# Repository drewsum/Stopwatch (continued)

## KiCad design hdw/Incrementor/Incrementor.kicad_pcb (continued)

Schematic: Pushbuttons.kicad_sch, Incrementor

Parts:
C701, C705, C706: 10nF; C_0603; Voltage 50V; Digi-Key PN 1276-1921-1-ND
C702, C703, C704, C707, C708, C709, C712, C713, C715, C717: 0.1uF; C_0603; Voltage 50V; Digi-Key PN 311-1344-1-ND
C710, C711, C714: 10uF; C_0603; Voltage 10V; Digi-Key PN 490-14372-1-ND
R701, R702, R703: 499; R_0603; Tolerance 1%; Digi-Key PN P499HCT-ND
R704, R705, R706, R707, R708, R709, R710, R711, R712: 10k; R_0603; Tolerance 1%; Digi-Key PN RMCF0603FT10K0CT-ND
SW701, SW702, SW703: Cap_Touch; Capacitive_Touch_Pad
U701, U707, U708: AT42QT1010-TSHR; SOT-23-6; Digi-Key PN AT42QT1010-TSHRCT-ND
U702, U703, U706: TLV71330PDBV; SOT-23-5; Digi-Key PN 296-40658-1-ND
U704: 74LVC1G80; SOT-353_SC-70-5; Digi-Key PN 296-9852-1-ND
U705, U709, U710: 74LVC1G17; SOT-353_SC-70-5; Digi-Key PN 296-11934-1-ND

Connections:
+3V3: C702.1, C703.1, C704.1, C712.1, C713.1, C715.1, C717.1, U702.1 (IN), U702.3 (EN), U703.1 (IN), U703.3 (EN), U704.5 (VCC), U705.5 (VCC), U706.1 (IN), U706.3 (EN), U709.5 (VCC), U710.5 (VCC); also elsewhere on the board
Count_Reset: R712.1, U709.4; also elsewhere on the board
Display_Enable: R705.1, U704.1 (D), U704.4 (~Q); also elsewhere on the board
GND: C702.2, C703.2, C704.2, C707.2, C708.2, C709.2, C710.2, C711.2, C712.2, C713.2, C714.2, C715.2, C717.2, R704.2, R705.2, R706.2, R707.2, R711.2, R712.2, U701.2 (VSS), U702.2 (GND), U703.2 (GND), U704.3 (GND), U705.3 (GND), U706.2 (GND), U707.2 (VSS), U708.2 (VSS), U709.3 (GND), U710.3 (GND); also elsewhere on the board
unnamed: C701.1, U701.4 (SNS)
unnamed: C701.2, R701.2, U701.3 (SNSK)
unnamed: C705.1, U707.4 (SNS)
unnamed: C705.2, R702.2, U707.3 (SNSK)
unnamed: C706.1, U708.4 (SNS)
unnamed: C706.2, R703.2, U708.3 (SNSK)
unnamed: C707.1, U701.5 (VDD), U701.6 (SYNC), U702.5 (OUT)
unnamed: C708.1, U703.5 (OUT), U707.5 (VDD), U707.6 (SYNC)
unnamed: C709.1, U706.5 (OUT), U708.5 (VDD), U708.6 (SYNC)
unnamed: C710.1, R709.1, U709.2
unnamed: C711.1, R710.1, U710.2
unnamed: C714.1, R708.1, U705.2
unnamed: R701.1, SW701.1
unnamed: R702.1, SW702.1
unnamed: R703.1, SW703.1
unnamed: R704.1, R708.2, U701.1 (OUT)
unnamed: R706.1, R709.2, U707.1 (OUT)
unnamed: R707.1, R710.2, U708.1 (OUT)
unnamed: R711.1, U704.2 (C), U705.4
Source_Select: U710.4; also elsewhere on the board

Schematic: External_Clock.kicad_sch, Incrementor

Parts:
C801: 0.1uF; C_0603; Voltage 50V; Digi-Key PN 311-1344-1-ND
D801: 3.3V; D_SOD-323; Digi-Key PN CDSOD323-T03SCT-ND
J801: CLK_IN; Socket_Strip_Angled_1x02_Pitch2.54mm; Digi-Key PN SAM1225-02-ND
R801, R803: 100; R_0603; Tolerance 1%; Digi-Key PN RMCF0603FT100RCT-ND
R802: 10k; R_0603; Tolerance 1%; Digi-Key PN RMCF0603FT10K0CT-ND
U801: 74LVC1G17; SOT-353_SC-70-5; Digi-Key PN 296-11934-1-ND

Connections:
+3V3: C801.1, R802.1, U801.5 (VCC); also elsewhere on the board
External_Clock: U801.4; also elsewhere on the board
GND: C801.2, D801.2 (A2), J801.2, U801.3 (GND); also elsewhere on the board
unnamed: D801.1 (A1), R801.2, R802.2, R803.1
unnamed: J801.1, R801.1
unnamed: R803.2, U801.2

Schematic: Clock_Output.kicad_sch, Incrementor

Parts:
C1901: 0.1uF; C_0603; Voltage 50V; Digi-Key PN 311-1344-1-ND
D1901: 3.3V; D_SOD-323; Digi-Key PN CDSOD323-T03SCT-ND
J1901: CLK_OUT; Socket_Strip_Angled_1x02_Pitch2.54mm; Digi-Key PN SAM1225-02-ND
R1901, R1903: 100; R_0603; Tolerance 1%; Digi-Key PN RMCF0603FT100RCT-ND
R1902: 10k; R_0603; Tolerance 1%; Digi-Key PN RMCF0603FT10K0CT-ND
U1901: 74LVC1G17; SOT-353_SC-70-5; Digi-Key PN 296-11934-1-ND

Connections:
+3V3: C1901.1, R1902.1, U1901.5 (VCC); also elsewhere on the board
GND: C1901.2, D1901.2 (A2), J1901.2, U1901.3 (GND); also elsewhere on the board
unnamed: D1901.1 (A1), R1901.2, R1902.2, R1903.1
unnamed: J1901.1, R1903.2
unnamed: R1901.1, U1901.4
Stage10_Clock_Out: U1901.2; also elsewhere on the board

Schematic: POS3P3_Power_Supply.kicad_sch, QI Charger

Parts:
C301: 10uF; C_1206; Voltage 25V; Digi-Key PN 1276-7031-1-ND
C302: 10nF; C_0603; Voltage 50V; Digi-Key PN 1276-1921-1-ND
C303: 0.1uF; C_0603; Voltage 50V; Digi-Key PN 490-8020-1-ND
C307, C308: 22uF; C_1206; Voltage 10V; Digi-Key PN 1276-3148-1-ND
L301: 2.2u; L_Vishay_IHLP-2020; Tolerance 20%; Digi-Key PN 541-1236-1-ND
R301: 10k; R_0603; Tolerance 1%; Digi-Key PN RHM10KADCT-ND
R302: 100k; R_0603; Tolerance 1%; Digi-Key PN A106046CT-ND
R303: 10.5k; R_0603; Tolerance 1%; Digi-Key PN 311-10.5KHRCT-ND
R304: 562k; R_0603; Tolerance 1%; Digi-Key PN 311-562KHRCT-ND
R305: 180k; R_0603; Tolerance 1%; Digi-Key PN 749-1763-1-ND
TP301: TP; Test_Point
U301: TPS62130; QFN-16-1EP_3x3mm_Pitch0.5mm; Digi-Key PN 296-37878-1-ND

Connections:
+3V3: L301.2, R301.1, R304.1, TP301.1, U301.14 (VOS); also elsewhere on the board
+12V: C301.1, C303.1, R302.1, U301.10 (AVIN), U301.11 (PVIN), U301.12 (PVIN); also elsewhere on the board
GND: C301.2, C302.2, C303.2, R303.2, R305.2, U301.6 (AGND), U301.7 (FSW), U301.8 (DEF), U301.15 (PGND), U301.16 (PGND), U301.17 (EP); also elsewhere on the board
unnamed: C302.1, U301.9 (SS/TR)
unnamed: L301.1, U301.1 (SW), U301.2 (SW), U301.3 (SW)
unnamed: R302.2, R303.1, U301.13 (EN)
unnamed: R304.2, R305.1, U301.5 (FB)
POS3P3_PGOOD: R301.2, U301.4 (PG); also elsewhere on the board

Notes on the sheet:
03. +5V Power Supply

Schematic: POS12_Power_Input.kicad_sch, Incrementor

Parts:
C201: 0.1uF; C_0603; Voltage 50V; Digi-Key PN 311-1344-1-ND
C202, C204: 10nF; C_0603; Voltage 50V; Digi-Key PN 1276-1921-1-ND
C203: 1nF; C_0603; Voltage 50V; Digi-Key PN 1276-1018-1-ND
C205: 100uF; CP_Tantalum_Case-X_EIA-7343-43_Reflow; Voltage 16V; Tolerance 10%; Digi-Key PN 718-1102-1-ND
D201: 24V; D_SMA; Digi-Key PN SMAJ24CALFCT-ND
J201: +12V IN; BARREL_JACK; Digi-Key PN CP-202BH-ND
N201: +12V 1A Power Supply; Digi-Key PN 993-1335-ND
R201: 51.1k; R_0603; Tolerance 1%; Digi-Key PN RMCF0603FT10K0CT-ND
R202: 1.15k; R_0603; Tolerance 1%; Digi-Key PN RMCF0603FT10K0CT-ND
R203: 5.11k; R_0603; Tolerance 1%; Digi-Key PN RMCF0603FT10K0CT-ND
R204, R206: 10k; R_0603; Tolerance 1%; Digi-Key PN RMCF0603FT10K0CT-ND
R205: 6.04k; R_0603; Tolerance 1%; Digi-Key PN RMCF0603FT10K0CT-ND
R207: 16.5k; R_0603; Tolerance 1%; Digi-Key PN RMCF0603FT10K0CT-ND
TP201: TP; Pin_Header_Angled_1x01_Pitch2.54mm; Digi-Key PN 36-5005-ND
TP202, TP203: TP_Pad; Test_Point
U201: TPS26600RHFT; QFN-24-1EP_4x5mm_Pitch0.5mm; Digi-Key PN 296-45478-1-ND

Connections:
+3V3: R206.1; also elsewhere on the board
+12V: C205.1, TP203.1, U201.23 (OUT), U201.24 (OUT); also elsewhere on the board
+12Vin: C201.1, C202.1, C203.1, D201.1 (A1), J201.1, R201.1, R204.1, TP202.1, U201.8 (IN), U201.9 (IN)
GND: C201.2, C202.2, C203.2, C205.2, D201.2 (A2), J201.2, J201.3, TP201.1, U201.17 (GND); also elsewhere on the board
unnamed: C204.1, U201.20 (dVdT)
unnamed: C204.2, R203.2, R205.2, R207.2, U201.15 (RTN), U201.25 (RTN_PAD)
unnamed: R201.2, R202.1, U201.10 (UVLO)
unnamed: R202.2, R203.1, U201.12 (NC)
unnamed: R204.2, U201.14 (~SHDN)
unnamed: R205.1, U201.19 (ILIM)
unnamed: R207.1, U201.18 (IMON)
POS12_PGOOD: R206.2, U201.22 (~FLT); also elsewhere on the board

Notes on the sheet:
UVLO threshold set to 10.8V OVLO threshold set to 13.2V MODE set to Circuit Breaker with Auto-Retry

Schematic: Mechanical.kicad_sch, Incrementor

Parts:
H2001, H2002, H2003, H2004: 3mm; MountingHole_3mm
MK2001, MK2002, MK2003, MK2004: 4-40; Digi-Key PN 36-9900-ND
MK2005, MK2006, MK2007, MK2008: 4-40; Digi-Key PN 36-1892-ND

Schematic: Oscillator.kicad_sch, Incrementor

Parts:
C401, C404, C407: 0.1uF; C_0603; Voltage 50V; Digi-Key PN 311-1344-1-ND
C402: 10nF; C_0603; Voltage 50V; Digi-Key PN 1276-1921-1-ND
C403: 1nF; C_0603; Voltage 50V; Digi-Key PN 1276-1018-1-ND
R401, R402, R403, R404: 10k; R_0603; Tolerance 1%; Digi-Key PN RMCF0603FT10K0CT-ND
U401: CD4024; TSSOP-14_4.4x5mm_Pitch0.65mm; Digi-Key PN 296-49578-ND
U402: CD4040; DHVQFN16-1ep_3p5x2p5mm; Digi-Key PN 1727-7992-1-ND
X401: ECS-327KE; Digi-Key PN XC1751CT-ND

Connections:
1Hz_Clock: U402.13 (Q7); also elsewhere on the board
4Hz_Clock: U402.2 (Q5); also elsewhere on the board
16Hz_Clock: U402.5 (Q3); also elsewhere on the board
256Hz_Clock: R403.1, U401.3 (Q6), U402.10 (CLK); also elsewhere on the board
32768Hz_Clock: R401.1, U401.1 (~CP), X401.3 (OUT); also elsewhere on the board
+3V3: C401.1, C402.1, C403.1, C404.1, C407.1, U401.14 (VCC), U402.16 (VDD), X401.1 (EN), X401.4 (Vdd); also elsewhere on the board
Count_Reset: R402.1, R404.1, U401.2 (MR), U402.11 (Reset); also elsewhere on the board
GND: C401.2, C402.2, C403.2, C404.2, C407.2, R401.2, R402.2, R403.2, R404.2, U401.7 (GND), U402.8 (VSS), U402.17, X401.2 (GND); also elsewhere on the board

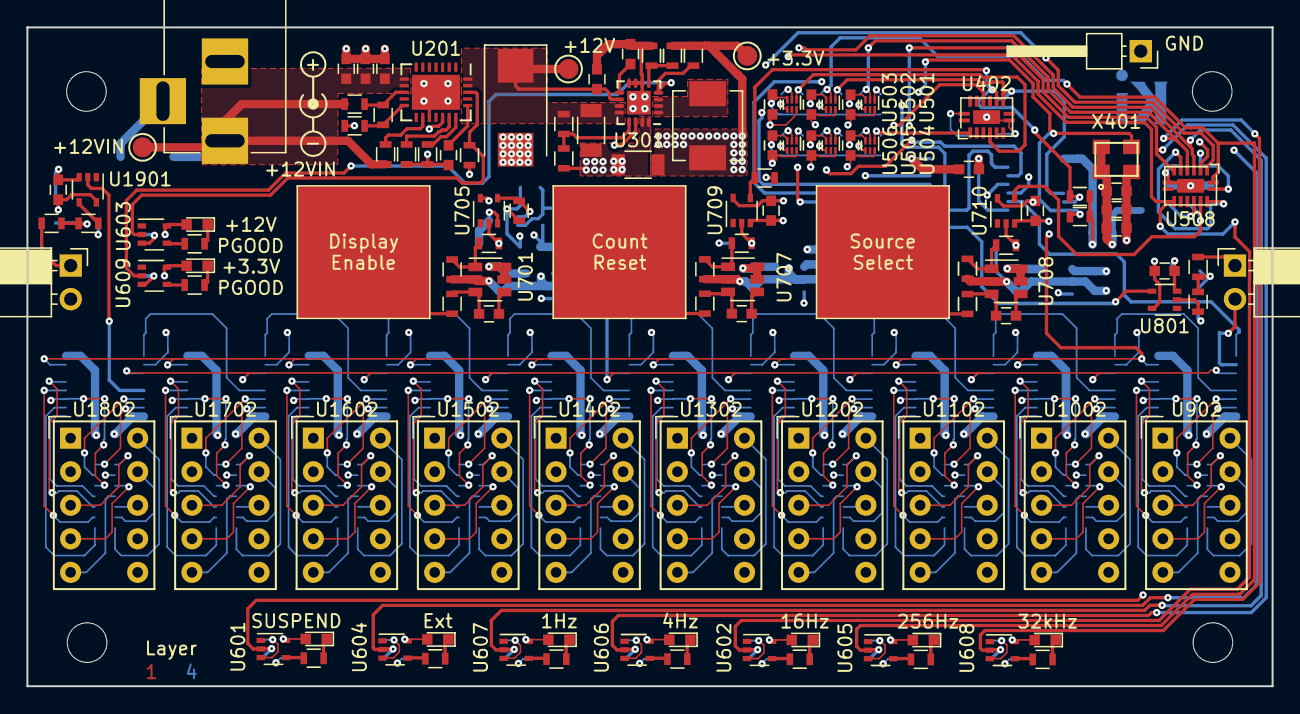
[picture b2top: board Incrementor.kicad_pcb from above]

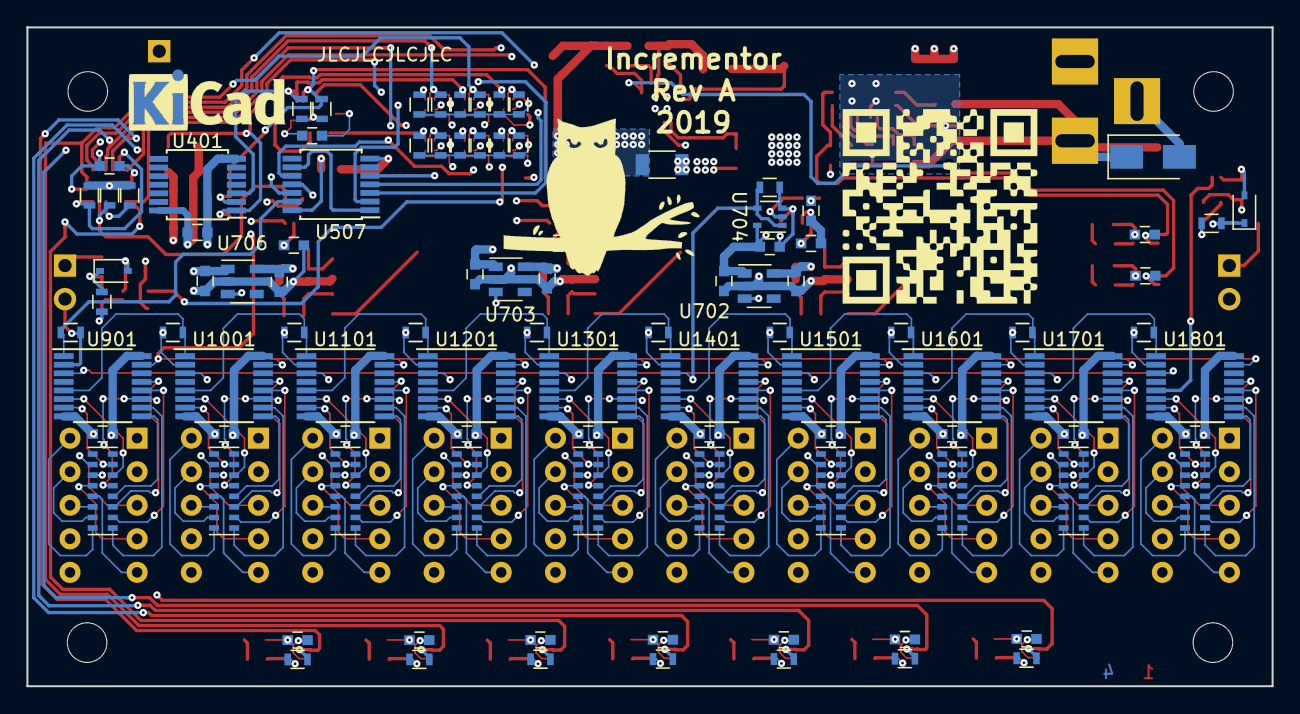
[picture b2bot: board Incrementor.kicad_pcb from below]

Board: 4 copper layers, 94.3 x 49.9 mm, 226 parts (92 on the bottom side), 236 nets.

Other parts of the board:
C304, C305: 22uF; C_1206

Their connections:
+3V3: C304.1, C305.1; also elsewhere on the board
GND: C304.2, C305.2; also elsewhere on the board

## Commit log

2019-09-01 Added kicad project, started schematic
2019-09-01 Added duplicate stage pages, oscillator
2019-09-01 Added a lot more schematic cheets
2019-09-04 Added more schematic sheets
2019-09-05 fixing branch
2019-09-07 Reordered schematic sheets
2019-09-07 Assigned REFDESs
2019-09-07 Assigned Digi Key PNs and footprints
2019-09-07 Fixed library references, completed ERC
2019-09-24 Migrated to kicad 5 footprint libs, pulled changes into PCB
2019-09-24 Started PCB
2019-09-24 More routing
2019-11-21 Changed input protection circuit
2019-12-06 Added new power supply, more layout
2019-12-08 Added cap touch LDOs to make the circuit not suck
2019-12-09 Finished arranging parts, drew board outline
2019-12-09 PCB arrangemnt refinements
2019-12-10 Lots and lots of board compression. Now fits in 10cmx5cm
2019-12-11 Started routing, fixed AND gate pinout
2019-12-12 lots more routing
2019-12-14 Finished first pass on routing
2019-12-15 Added lots of PCB symbols/features
2019-12-15 Fixed a few BOM issues
2019-12-15 Fixed issues, generated gerbers
2023-12-30 ported to kicad 7.0 from old project
2024-01-02 renamed project, removed stuff I dont need
2024-01-02 renamed folders
2024-01-02 started sch work
2024-01-05 adjusted stage sheet
2024-01-05 added reset stuff
2024-01-08 added more reset stuff
2024-01-08 copied to minutes reset sheet
2024-01-11 added some more junk
2024-01-17 Assigned some digikey pns
2024-01-18 added ability to turn off colons
2024-01-19 added proper power sequencing, discharge
2024-01-23 pulled footprints into layout
2024-01-24 hid unneeded refdes in layout
2024-01-25 some random layout stuff
2024-01-25 more component placement
2024-01-27 more component placment
2024-01-30 lots and lots of routing
2024-01-30 got no unconnects to 0
2024-01-30 added some silkscreen stuff
2024-02-03 generated gerbers
2024-04-16 generated rev b folder
2024-04-16 ported rev b to kicad 8
2024-04-16 converted pcb to rev b
2024-04-16 integrated SC70 gates
2024-04-16 some rev B PCB progress
2024-04-16 moved all components into rev b board outline
2024-04-19 more PCB work
2024-04-28 finished rev B PCB
